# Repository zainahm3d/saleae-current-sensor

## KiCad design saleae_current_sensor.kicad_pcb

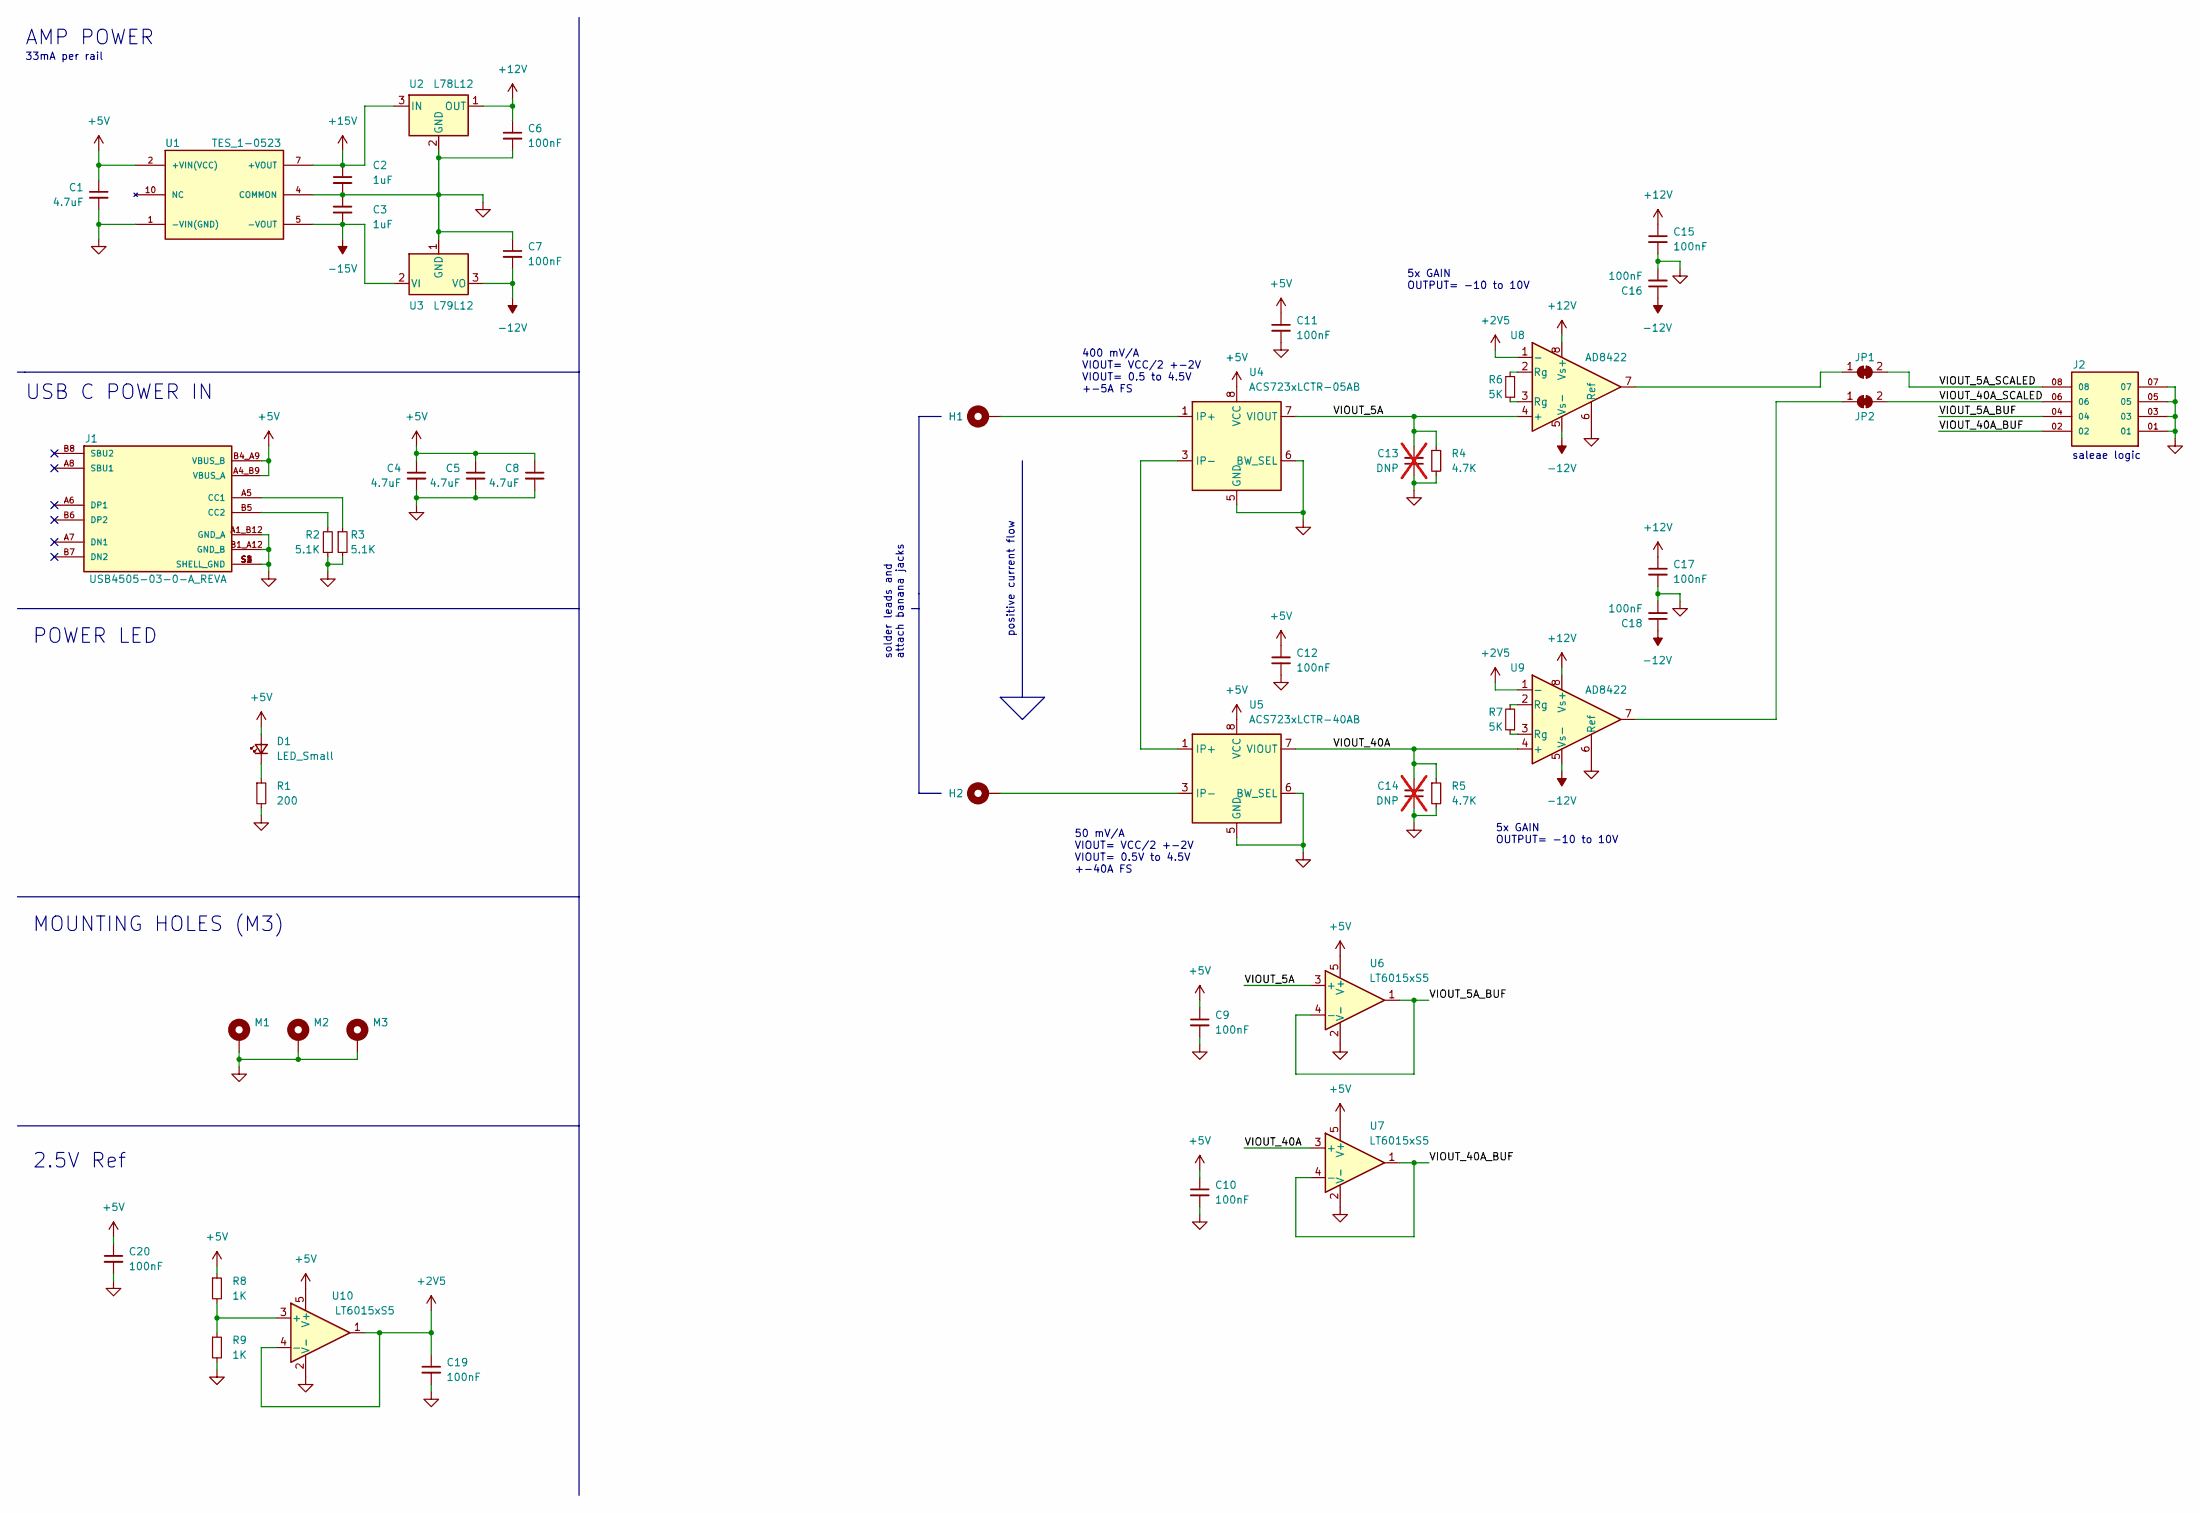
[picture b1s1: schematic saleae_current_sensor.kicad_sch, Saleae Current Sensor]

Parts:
C1, C4, C5, C8: 4.7uF; C_1206_3216Metric
C2, C3: 1uF; C_1206_3216Metric
C6, C7, C9, C10, C11, C12, C15, C16, C17, C18, C19, C20: 100nF; C_0603_1608Metric
C13, C14: DNP; C_0603_1608Metric; not fitted
D1: LED_Small; LED_1206_3216Metric
H1: IP; MountingHole_2.7mm_M2.5_ISO7380_Pad_TopBottom
H2: IN; MountingHole_2.7mm_M2.5_ISO7380_Pad_TopBottom
J1: USB4505-03-0-A_REVA; GCT_USB4505-03-0-A_REVA; PARTREV A
J2: TSM-104-02-T-DH; SAMTEC_TSM-104-02-T-DH; PARTREV R
JP1, JP2: SolderJumper_2_Bridged; SolderJumper-2_P1.3mm_Bridged2Bar_Pad1.0x1.5mm
M1, M2, M3: MountingHole_Pad; MountingHole_3.2mm_M3_ISO7380_Pad_TopBottom
R1: 200; R_0603_1608Metric
R2, R3: 5.1K; R_0603_1608Metric
R4, R5: 4.7K; R_0603_1608Metric
R6, R7: 5K; R_0603_1608Metric
R8, R9: 1K; R_0603_1608Metric
U1: TES_1-0523; CONV_TES_1-0523; PARTREV June 23, 2020
U2: L78L12; SOT-89-3
U3: L79L12; SOT-89-3
U4: ACS723xLCTR-05AB; SOIC-8_3.9x4.9mm_P1.27mm
U5: ACS723xLCTR-40AB; SOIC-8_3.9x4.9mm_P1.27mm
U6, U7, U10: LT6015xS5; SOT-23-5
U8, U9: AD8422; SOP65P490X110-8N

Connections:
+2V5: C19.1, U8.1 (-), U9.1 (-), U10.1, U10.4 (-)
+5V: C1.1, C4.1, C5.1, C8.1, C9.1, C10.1, C11.1, C12.1, C20.1, D1.2 (A), J1.A4_B9 (VBUS_A), J1.B4_A9 (VBUS_B), R8.1, U1.2 (+VIN(VCC)), U4.8 (VCC), U5.8 (VCC), U6.5 (V+), U7.5 (V+), U10.5 (V+)
+12V: C6.1, C15.1, C17.1, U2.1 (OUT), U8.8 (Vs+), U9.8 (Vs+)
+15V: C2.1, U1.7 (+VOUT), U2.3 (IN)
-12V: C7.2, C16.1, C18.1, U3.3 (VO), U8.5 (Vs-), U9.5 (Vs-)
-15V: C3.2, U1.5 (-VOUT), U3.2 (VI)
/VIOUT_5A: C13.2, R4.1, U4.7 (VIOUT), U6.3 (+), U8.4 (+)
/VIOUT_5A_BUF: J2.04, U6.1, U6.4 (-)
/VIOUT_5A_SCALED: J2.08, JP1.2 (B)
/VIOUT_40A: C14.2, R5.1, U5.7 (VIOUT), U7.3 (+), U9.4 (+)
/VIOUT_40A_BUF: J2.02, U7.1, U7.4 (-)
/VIOUT_40A_SCALED: J2.06, JP2.2 (B)
GND: C1.2, C2.2, C3.1, C4.2, C5.2, C6.2, C7.1, C8.2, C9.2, C10.2, C11.2, C12.2, C13.1, C14.1, C15.2, C16.2, C17.2, C18.2, C19.2, C20.2, J1.A1_B12 (GND_A), J1.B1_A12 (GND_B), J1.S1 (SHELL_GND), J1.S2 (SHELL_GND), J1.S3 (SHELL_GND), J1.S4 (SHELL_GND), J2.01, J2.03, J2.05, J2.07, M1.1, M2.1, M3.1, R1.2, R2.1, R3.2, R4.2, R5.2, R9.2, U1.1 (-VIN(GND)), U1.4 (COMMON), U2.2 (GND), U3.1 (GND), U4.5 (GND), U4.6 (BW_SEL), U5.5 (GND), U5.6 (BW_SEL), U6.2 (V-), U7.2 (V-), U8.6 (Ref), U9.6 (Ref), U10.2 (V-)
unnamed: D1.1 (K), R1.1
unnamed: H1.1, U4.1 (IP+), U4.2 (IP+)
unnamed: H2.1, U5.3 (IP-), U5.4 (IP-)
unnamed: J1.A5 (CC1), R3.1
unnamed: J1.B5 (CC2), R2.2
unnamed: JP1.1 (A), U8.7
unnamed: JP2.1 (A), U9.7
unnamed: R6.1, U8.3 (Rg)
unnamed: R6.2, U8.2 (Rg)
unnamed: R7.1, U9.3 (Rg)
unnamed: R7.2, U9.2 (Rg)
unnamed: U4.3 (IP-), U4.4 (IP-), U5.1 (IP+), U5.2 (IP+)
unnamed: R8.2, R9.1, U10.3 (+)

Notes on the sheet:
50 mV/A VIOUT= VCC/2 +-2V VIOUT= 0.5V to 4.5V +-40A FS
solder leads and attach banana jacks
positive current flow
saleae logic
2.5V Ref
AMP POWER
POWER LED
MOUNTING HOLES (M3)
5x GAIN OUTPUT= -10 to 10V
33mA per rail
USB C POWER IN
400 mV/A VIOUT= VCC/2 +-2V VIOUT= 0.5 to 4.5V +-5A FS

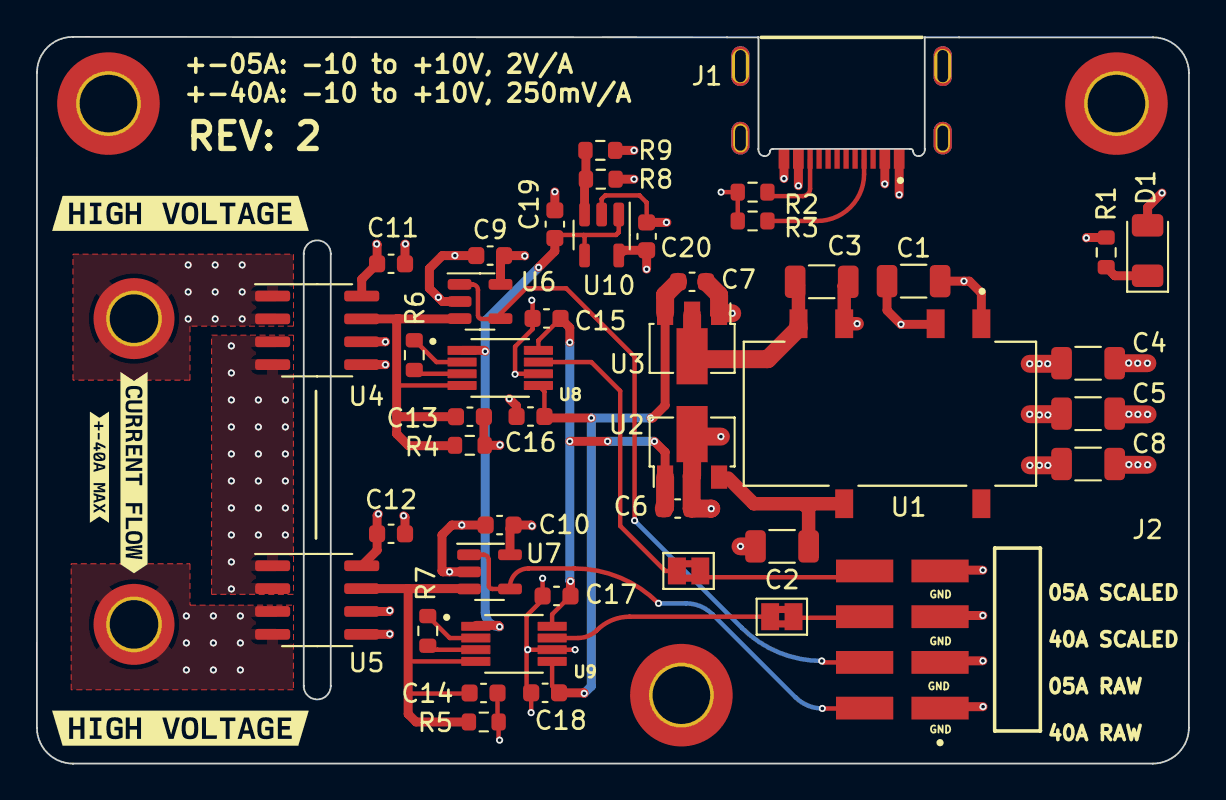
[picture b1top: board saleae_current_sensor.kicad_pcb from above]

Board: 4 copper layers, 64.0 x 40.4 mm, 54 parts (1 on the bottom side), 26 nets.

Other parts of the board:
kibuzzard-64A2F4F2: G***; kibuzzard-64A2F4F2
kibuzzard-64A2F4F7: G***; kibuzzard-64A2F4F7
kibuzzard-64A2F491: G***; kibuzzard-64A2F491
kibuzzard-64A244C5: G***; kibuzzard-64A244C5
kibuzzard-64A24575: G***; kibuzzard-64A24575

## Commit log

2022-12-05 [WIP] Initial commit
2022-12-26 Add buffers to raw signals Add connections for main power lines Annotate all components Assign all footprints
2022-12-30 Layout complete
2023-02-27 update to KiCAD 7
2023-03-18 kibot??
2023-03-25 Export outputs via GitHub Actions w/ KiCad CLI
2023-07-03 Misc updates kibuzzard lock in mounting holes/connectors change dielectric thickness for total 1.6mm stackup
2023-07-03 switch to prebuilt kicad image
2023-07-04 Misc updates kibuzzard lock in mounting holes/connectors change dielectric thickness for total 1.6mm stackup CI updates
2023-07-04 Final changes for JLCPCB order
2023-07-07 Route a gap between LV and HV sides of current sensors
2023-07-23 Add 2V5 voltage reference :( and reduce LED resistor
